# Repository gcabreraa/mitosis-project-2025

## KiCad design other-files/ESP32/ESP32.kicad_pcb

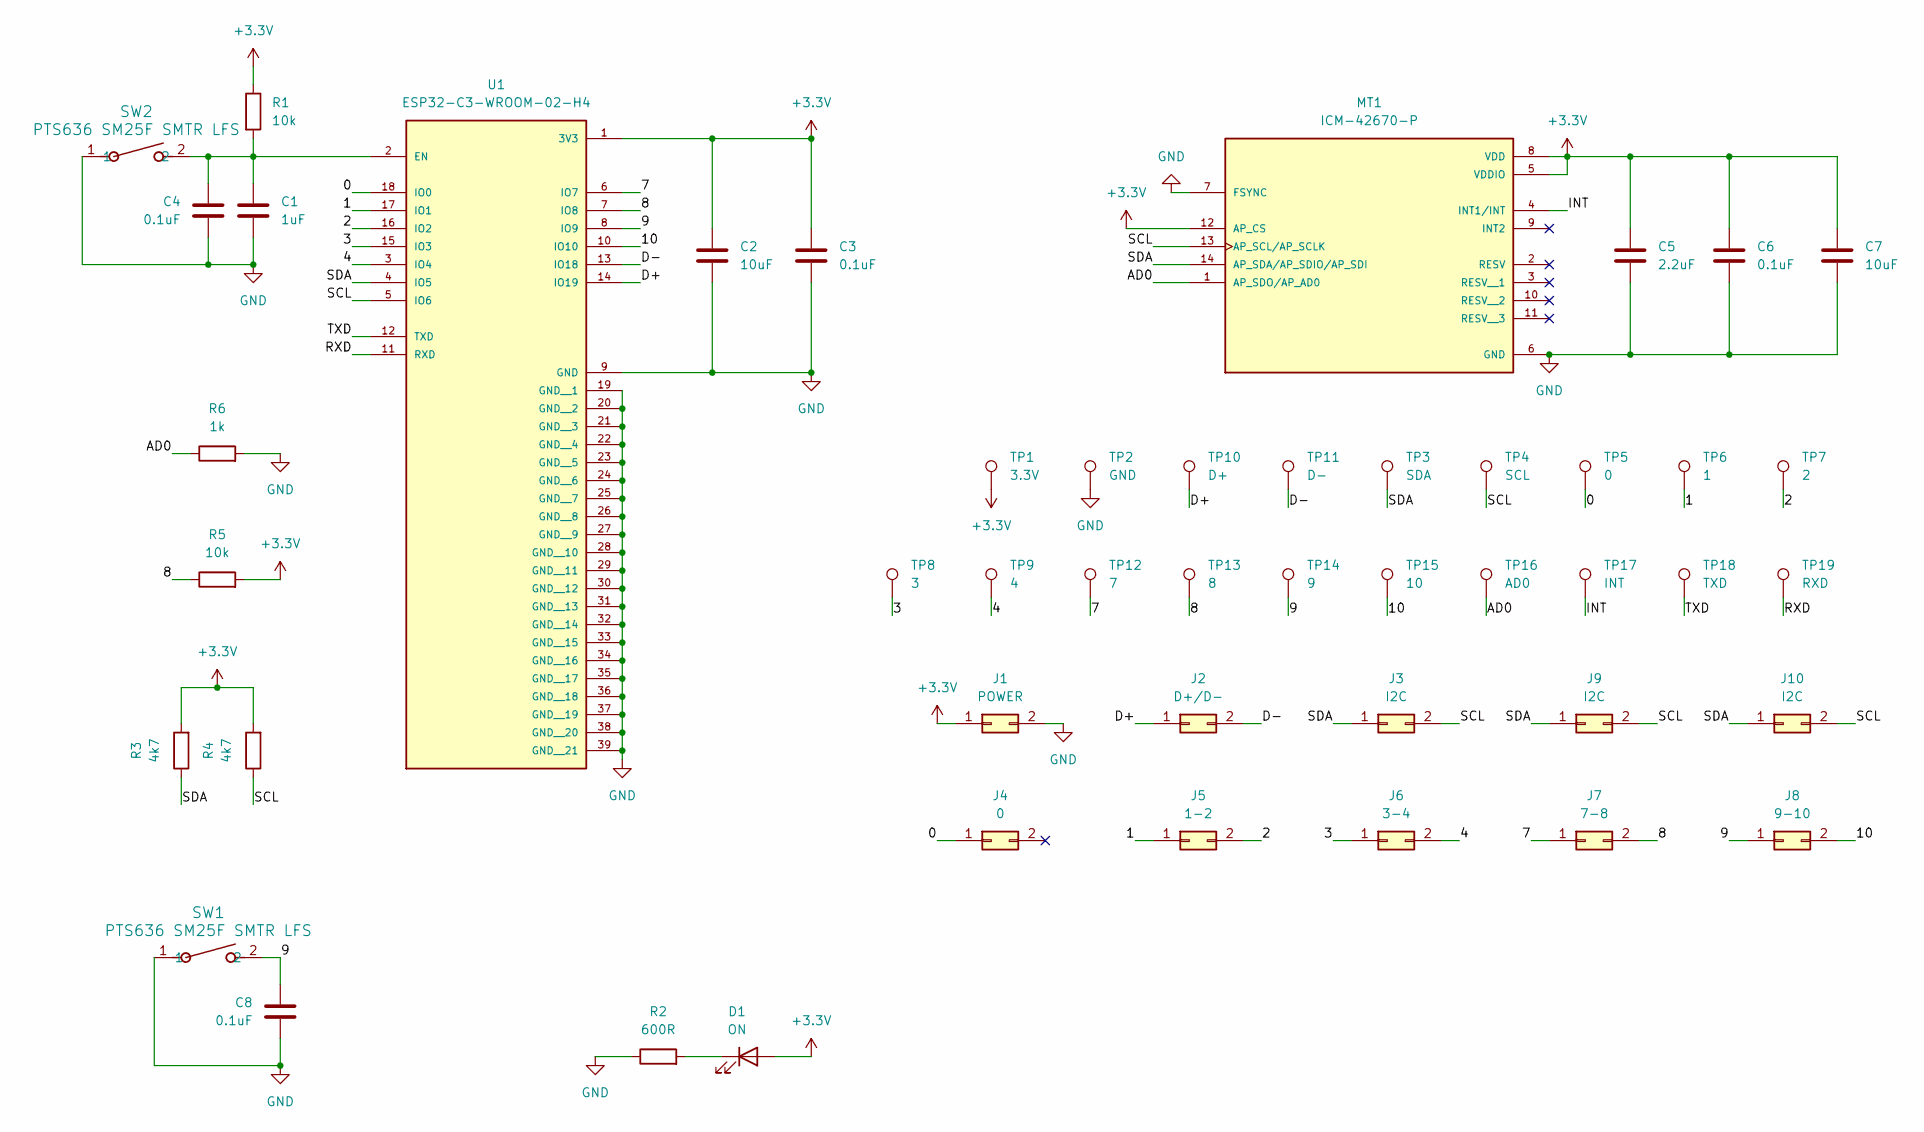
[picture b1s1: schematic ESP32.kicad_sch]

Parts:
C1: 1uF; C_0805_2012Metric_Pad1.18x1.45mm_HandSolder
C2, C7: 10uF; C_0805_2012Metric_Pad1.18x1.45mm_HandSolder
C3, C4, C6, C8: 0.1uF; C_0805_2012Metric_Pad1.18x1.45mm_HandSolder
C5: 2.2uF; C_0805_2012Metric_Pad1.18x1.45mm_HandSolder
D1: ON; LED_0805_2012Metric_Pad1.15x1.40mm_HandSolder
J1: POWER; PinHeader_2x01_P2.54mm_Vertical
J2: D+/D-; PinHeader_2x01_P2.54mm_Vertical
J3, J9, J10: I2C; PinHeader_2x01_P2.54mm_Vertical
J4: 0; PinHeader_2x01_P2.54mm_Vertical
J5: 1-2; PinHeader_2x01_P2.54mm_Vertical
J6: 3-4; PinHeader_2x01_P2.54mm_Vertical
J7: 7-8; PinHeader_2x01_P2.54mm_Vertical
J8: 9-10; PinHeader_2x01_P2.54mm_Vertical
MT1: ICM-42670-P; XDCR_ICM-42670-P; PARTREV 1.1
R1, R5: 10k; R_0805_2012Metric_Pad1.20x1.40mm_HandSolder
R2: 600R; R_0805_2012Metric_Pad1.20x1.40mm_HandSolder
R3, R4: 4k7; R_0805_2012Metric_Pad1.20x1.40mm_HandSolder
R6: 1k; R_0805_2012Metric_Pad1.20x1.40mm_HandSolder
SW1, SW2: PTS636 SM25F SMTR LFS; SW2_PTS636 SM25F SMTR LFS_CNK
TP1: 3.3V; TestPoint_THTPad_2.0x2.0mm_Drill1.0mm
TP2: GND; TestPoint_THTPad_2.0x2.0mm_Drill1.0mm
TP3: SDA; TestPoint_THTPad_2.0x2.0mm_Drill1.0mm
TP4: SCL; TestPoint_THTPad_2.0x2.0mm_Drill1.0mm
TP5: 0; TestPoint_THTPad_2.0x2.0mm_Drill1.0mm
TP6: 1; TestPoint_THTPad_2.0x2.0mm_Drill1.0mm
TP7: 2; TestPoint_THTPad_2.0x2.0mm_Drill1.0mm
TP8: 3; TestPoint_THTPad_2.0x2.0mm_Drill1.0mm
TP9: 4; TestPoint_THTPad_2.0x2.0mm_Drill1.0mm
TP10: D+; TestPoint_THTPad_2.0x2.0mm_Drill1.0mm
TP11: D-; TestPoint_THTPad_2.0x2.0mm_Drill1.0mm
TP12: 7; TestPoint_THTPad_2.0x2.0mm_Drill1.0mm
TP13: 8; TestPoint_THTPad_2.0x2.0mm_Drill1.0mm
TP14: 9; TestPoint_THTPad_2.0x2.0mm_Drill1.0mm
TP15: 10; TestPoint_THTPad_2.0x2.0mm_Drill1.0mm
TP16: AD0; TestPoint_THTPad_2.0x2.0mm_Drill1.0mm
TP17: INT; TestPoint_THTPad_2.0x2.0mm_Drill1.0mm
TP18: TXD; TestPoint_THTPad_2.0x2.0mm_Drill1.0mm
TP19: RXD; TestPoint_THTPad_2.0x2.0mm_Drill1.0mm
U1: ESP32-C3-WROOM-02-H4; MODULE_ESP32-C3-WROOM-02-H4

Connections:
+3.3V: C2.1, C3.1, C5.1, C6.1, C7.1, D1.2 (A), J1.1, MT1.5 (VDDIO), MT1.8 (VDD), MT1.12 (AP_CS), R1.1, R3.2, R4.2, R5.2, TP1.1, U1.1 (3V3)
/0: J4.1, TP5.1, U1.18 (IO0)
/1: J5.1, TP6.1, U1.17 (IO1)
/2: J5.2, TP7.1, U1.16 (IO2)
/3: J6.1, TP8.1, U1.15 (IO3)
/4: J6.2, TP9.1, U1.3 (IO4)
/7: J7.1, TP12.1, U1.6 (IO7)
/8: J7.2, R5.1, TP13.1, U1.7 (IO8)
/9: C8.1, J8.1, SW1.2, TP14.1, U1.8 (IO9)
/10: J8.2, TP15.1, U1.10 (IO10)
/AD0: MT1.1 (AP_SDO/AP_AD0), R6.1, TP16.1
/D+: J2.1, TP10.1, U1.14 (IO19)
/D-: J2.2, TP11.1, U1.13 (IO18)
/INT: MT1.4 (INT1/INT), TP17.1
/RXD: TP19.1, U1.11 (RXD)
/SCL: J3.2, J9.2, J10.2, MT1.13 (AP_SCL/AP_SCLK), R4.1, TP4.1, U1.5 (IO6)
/SDA: J3.1, J9.1, J10.1, MT1.14 (AP_SDA/AP_SDIO/AP_SDI), R3.1, TP3.1, U1.4 (IO5)
/TXD: TP18.1, U1.12 (TXD)
GND: C1.2, C2.2, C3.2, C4.2, C5.2, C6.2, C7.2, C8.2, J1.2, MT1.6 (GND), MT1.7 (FSYNC), R2.1, R6.2, SW1.1, SW2.1, TP2.1, U1.9 (GND), U1.19 (GND__1), U1.20 (GND__2), U1.21 (GND__3), U1.22 (GND__4), U1.23 (GND__5), U1.24 (GND__6), U1.25 (GND__7), U1.26 (GND__8), U1.27 (GND__9), U1.28 (GND__10), U1.29 (GND__11), U1.30 (GND__12), U1.31 (GND__13), U1.32 (GND__14), U1.33 (GND__15), U1.34 (GND__16), U1.35 (GND__17), U1.36 (GND__18), U1.37 (GND__19), U1.38 (GND__20), U1.39 (GND__21)
unnamed: D1.1 (K), R2.2
unnamed: C1.1, C4.1, R1.2, SW2.2, U1.2 (EN)

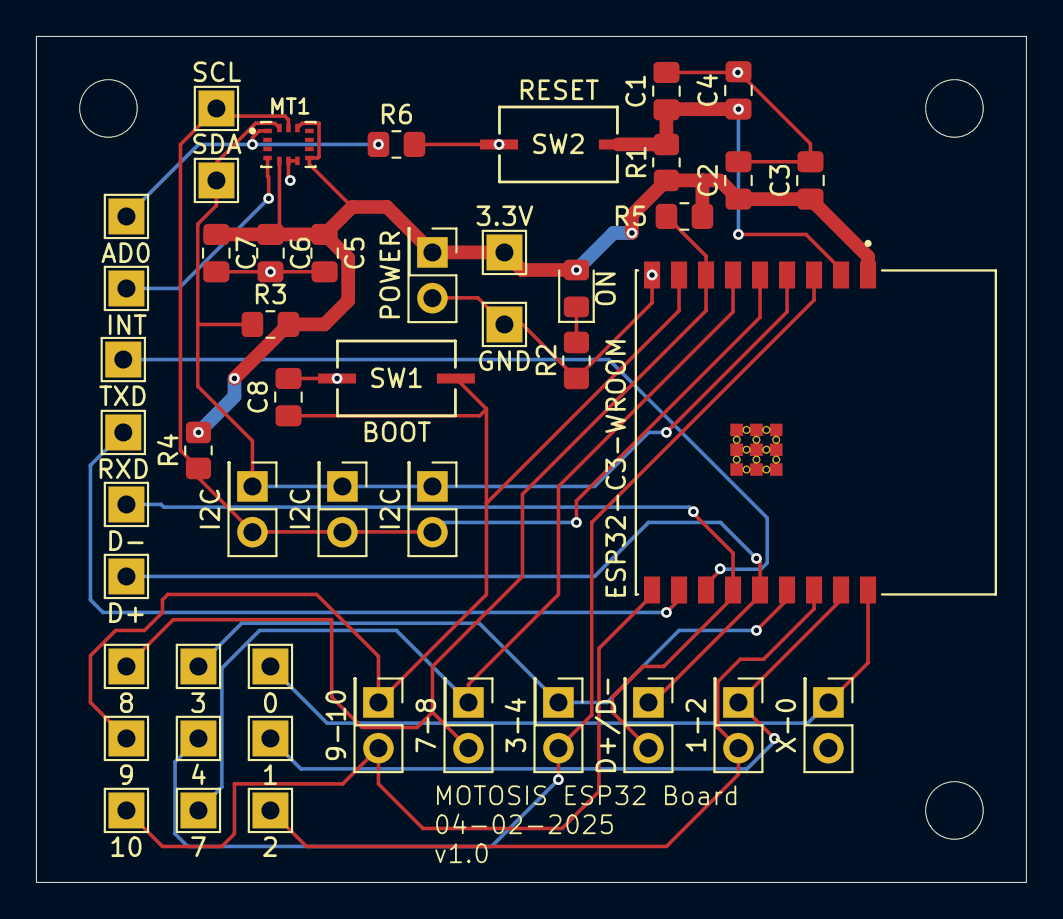
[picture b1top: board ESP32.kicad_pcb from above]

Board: 2 copper layers, 55.0 x 47.0 mm, 48 parts (0 on the bottom side), 21 nets.

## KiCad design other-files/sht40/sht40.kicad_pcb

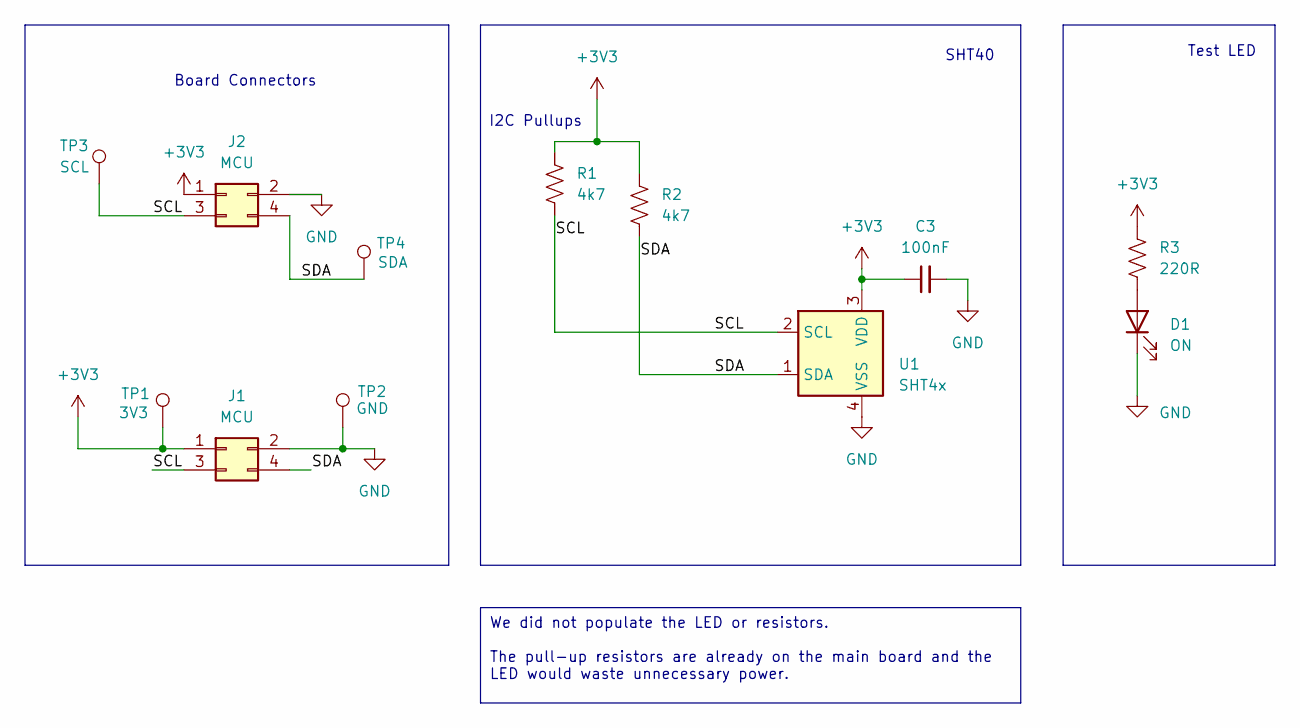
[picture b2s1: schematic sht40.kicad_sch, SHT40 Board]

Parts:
C3: 100nF; C_0805_2012Metric_Pad1.18x1.45mm_HandSolder
D1: ON; LED_0805_2012Metric_Pad1.15x1.40mm_HandSolder
J1, J2: MCU; PinHeader_2x02_P2.54mm_Vertical_SMD
R1, R2: 4k7; R_0805_2012Metric_Pad1.20x1.40mm_HandSolder
R3: 220R; R_0805_2012Metric_Pad1.20x1.40mm_HandSolder
TP1: 3V3; TestPoint_THTPad_2.0x2.0mm_Drill1.0mm
TP2: GND; TestPoint_THTPad_2.0x2.0mm_Drill1.0mm
TP3: SCL; TestPoint_THTPad_2.0x2.0mm_Drill1.0mm
TP4: SDA; TestPoint_THTPad_2.0x2.0mm_Drill1.0mm
U1: SHT4x; Sensirion_DFN-4_1.5x1.5mm_P0.8mm_SHT4x_NoCentralPad

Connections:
+3V3: C3.1, J1.1, J2.1, R1.2, R2.1, R3.2, TP1.1, U1.3 (VDD)
/SCL: J1.3, J2.3, R1.1, TP3.1, U1.2 (SCL)
/SDA: J1.4, J2.4, R2.2, TP4.1, U1.1 (SDA)
GND: C3.2, D1.1 (K), J1.2, J2.2, TP2.1, U1.4 (VSS)
unnamed: D1.2 (A), R3.1

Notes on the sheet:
We did not populate the LED or resistors. The pull-up resistors are already on the main board and the LED would waste unnecessary power.
I2C Pullups
Test LED
SHT40
Board Connectors

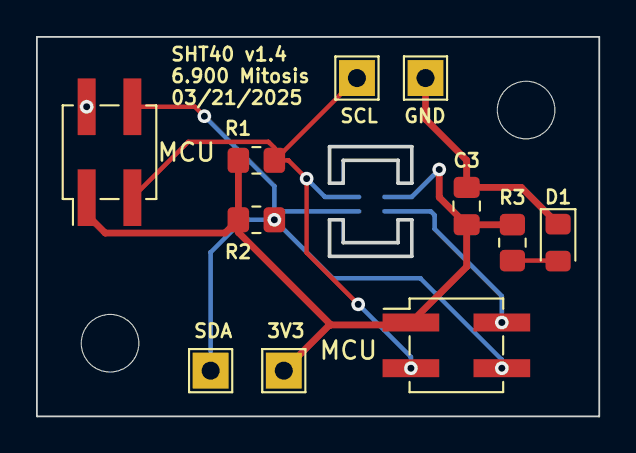
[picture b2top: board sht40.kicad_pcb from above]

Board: 2 copper layers, 31.1 x 21.0 mm, 12 parts (1 on the bottom side), 5 nets.

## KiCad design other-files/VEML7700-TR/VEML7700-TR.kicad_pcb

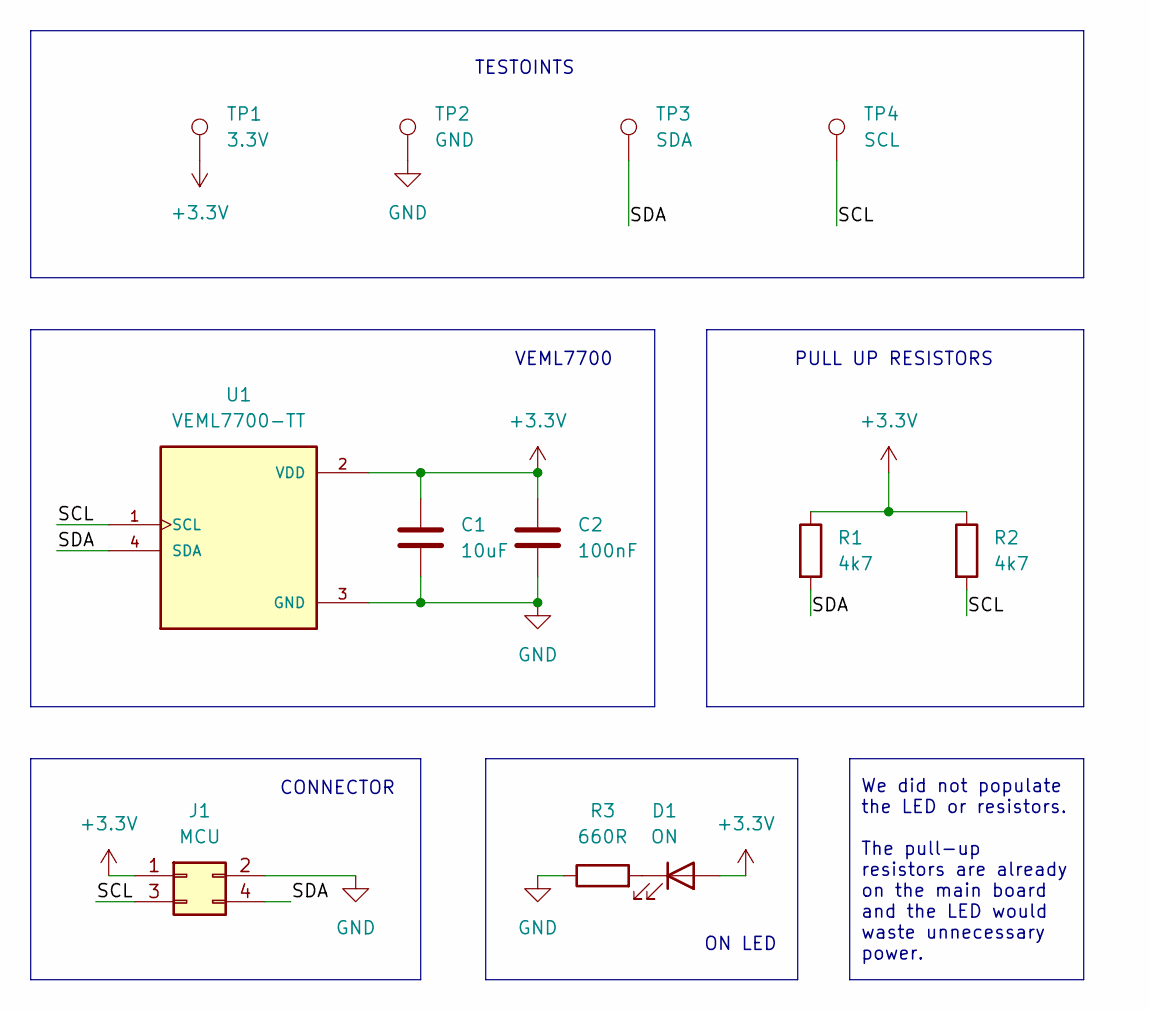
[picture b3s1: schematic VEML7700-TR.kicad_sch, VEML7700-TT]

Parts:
C1: 10uF; C_0805_2012Metric_Pad1.18x1.45mm_HandSolder
C2: 100nF; C_0805_2012Metric_Pad1.18x1.45mm_HandSolder
D1: ON; LED_0805_2012Metric_Pad1.15x1.40mm_HandSolder
J1: MCU; PinHeader_2x02_P2.54mm_Vertical_SMD
R1, R2: 4k7; R_0805_2012Metric_Pad1.20x1.40mm_HandSolder
R3: 660R; R_0805_2012Metric_Pad1.20x1.40mm_HandSolder
TP1: 3.3V; TestPoint_THTPad_2.0x2.0mm_Drill1.0mm
TP2: GND; TestPoint_THTPad_2.0x2.0mm_Drill1.0mm
TP3: SDA; TestPoint_THTPad_2.0x2.0mm_Drill1.0mm
TP4: SCL; TestPoint_THTPad_2.0x2.0mm_Drill1.0mm
U1: VEML7700-TT; XDCR_VEML7700-TT; PARTREV 1.6

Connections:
+3.3V: C1.1, C2.1, D1.2 (A), J1.1, R1.1, R2.1, TP1.1, U1.2 (VDD)
/SCL: J1.3, R2.2, TP4.1, U1.1 (SCL)
/SDA: J1.4, R1.2, TP3.1, U1.4 (SDA)
GND: C1.2, C2.2, J1.2, R3.1, TP2.1, U1.3 (GND)
unnamed: D1.1 (K), R3.2

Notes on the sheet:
We did not populate the LED or resistors. The pull-up resistors are already on the main board and the LED would waste unnecessary power.
VEML7700
TESTOINTS
ON LED
PULL UP RESISTORS
CONNECTOR

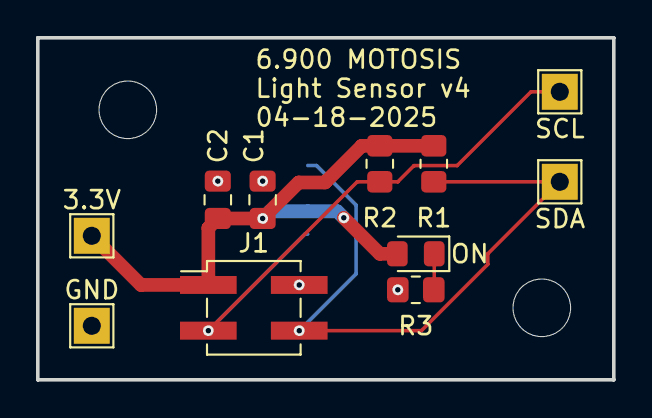
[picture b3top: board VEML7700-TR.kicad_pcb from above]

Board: 2 copper layers, 32.0 x 19.0 mm, 12 parts (1 on the bottom side), 5 nets.

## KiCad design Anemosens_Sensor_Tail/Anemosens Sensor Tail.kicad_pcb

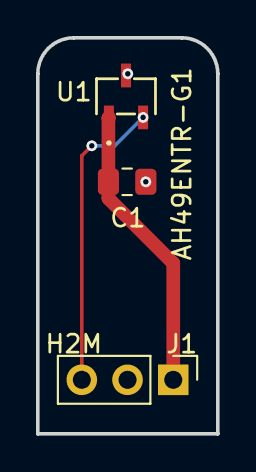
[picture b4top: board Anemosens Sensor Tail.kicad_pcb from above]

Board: 2 copper layers, 10.0 x 22.0 mm, 3 parts (0 on the bottom side), 3 nets.

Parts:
C1: 100nF; C_0805_2012Metric_Pad1.18x1.45mm_HandSolder
J1: H2M; PinHeader_1x03_P2.54mm_Vertical
U1: AH49ENTR-G1; SOT-23-3_DIO

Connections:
+3.3V: C1.1, J1.1, U1.1 (VCC)
/HALL_OUT: J1.3, U1.2 (OUT)
GND: C1.2, J1.2, U1.3 (GND)

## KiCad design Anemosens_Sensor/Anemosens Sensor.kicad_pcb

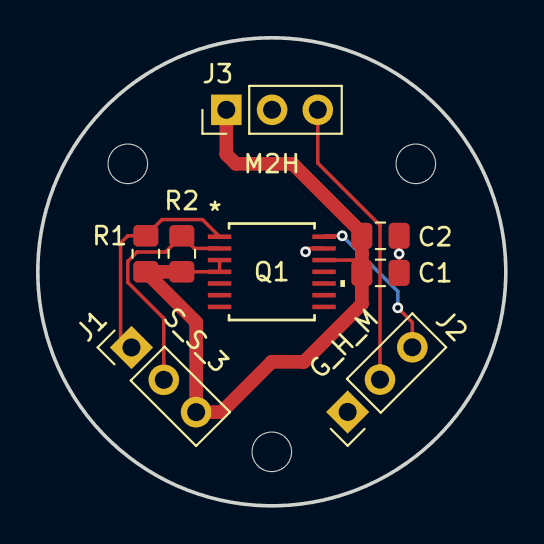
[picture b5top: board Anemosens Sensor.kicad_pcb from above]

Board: 2 copper layers, 26.0 x 26.0 mm, 8 parts (0 on the bottom side), 6 nets.

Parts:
C1: 100nF; C_0805_2012Metric_Pad1.18x1.45mm_HandSolder
C2: 10uF; C_0805_2012Metric_Pad1.18x1.45mm_HandSolder
J1: S_S_3; PinHeader_1x03_P2.54mm_Vertical
J2: G_H_M; PinHeader_1x03_P2.54mm_Vertical
J3: M2H; PinHeader_1x03_P2.54mm_Vertical
Q1: AS5048B-HTSP-500; TRANS_HTSP-500_AMS
R1, R2: 4k7; R_0805_2012Metric_Pad1.20x1.40mm_HandSolder

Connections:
+3.3V: C1.2, C2.2, J1.3, J3.1, Q1.3 (A2), Q1.4 (A1), Q1.12 (VDD3V), R1.1, R2.1
/HALL_OUT: J2.2, J3.3
/MAG_INT: J2.3, Q1.14 (PWM)
/SCL: J1.2, Q1.2 (SCL), R2.2
/SDA: J1.1, Q1.1 (SDA), R1.2
GND: C1.1, C2.1, J2.1, J3.2, Q1.13 (GND)

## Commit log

2025-11-21 firmware main files
2025-11-21 Other project files
2025-11-21 Project files
2025-11-21 Final project files
